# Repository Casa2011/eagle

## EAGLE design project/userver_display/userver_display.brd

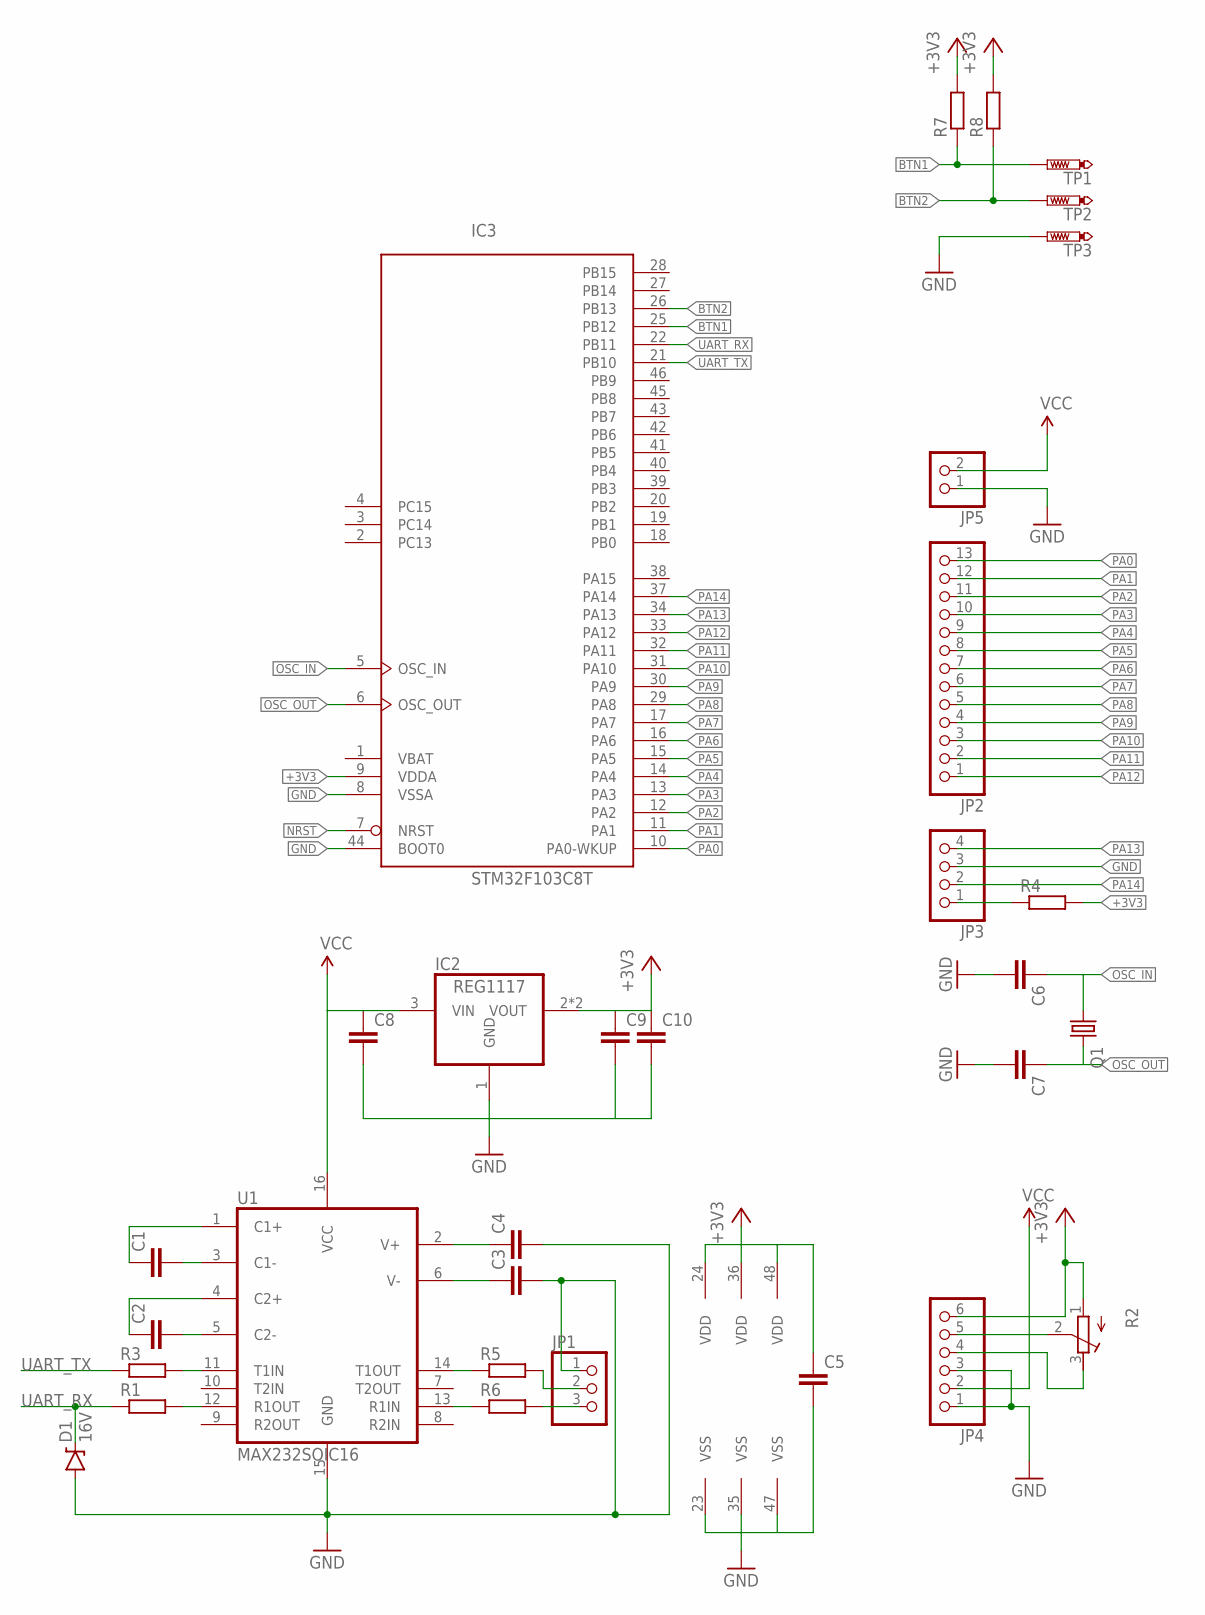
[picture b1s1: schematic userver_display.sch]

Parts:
C1, C2, C3, C4, C5, C8, C9, C10: CC0805; C0805
C6, C7: CC0603; C0603
D1: 16V; SOD-123
IC2: REG1117; SOT223
IC3: STM32F103C8T; LQFP48
JP1: PINHD-1X3; 1X03
JP2: PINHD-1X13; 1X13
JP3: PINHD-1X4; 1X04
JP4: PINHD-1X6; 1X06
JP5: PINHD-1X2; 1X02
Q1: CRYSTALHC49UP; HC49UP
R1, R3, R4, R5, R6, R7, R8: R0603; 0603
R2: R-TRIMM64P; RTRIM64P
TP1, TP2, TP3: PTR1TP10SQ; TP10SQ
U1: MAX232SOIC16; SO016

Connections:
+3V3: C5.1, C9.1, C10.1, IC2.2 (VOUT), IC2.4 (VOUT), IC3.9 (VDDA), IC3.24 (VDD), IC3.36 (VDD), IC3.48 (VDD), JP4.6, R2.1 (A), R4.2, R7.2, R8.2
BTN1: IC3.25 (PB12), R7.1, TP1.TP
BTN2: IC3.26 (PB13), R8.1, TP2.TP
GND: C3.2, C4.2, C5.2, C6.2, C7.2, C8.2, C9.2, C10.2, D1.A, IC2.1 (GND), IC3.8 (VSSA), IC3.23 (VSS), IC3.35 (VSS), IC3.44 (BOOT0), IC3.47 (VSS), JP1.1, JP3.3, JP4.1, JP4.3, JP5.1, TP3.TP, U1.15 (GND)
unnamed: JP1.2, R5.2
unnamed: JP1.3, R6.2
unnamed: C2.1, U1.4 (C2+)
unnamed: C2.2, U1.5 (C2-)
unnamed: C1.2, U1.3 (C1-)
unnamed: C1.1, U1.1 (C1+)
unnamed: C3.1, U1.6 (V-)
unnamed: R1.2, U1.12 (R1OUT)
unnamed: R3.2, U1.11 (T1IN)
unnamed: C4.1, U1.2 (V+)
unnamed: R6.1, U1.13 (R1IN)
unnamed: R5.1, U1.14 (T1OUT)
unnamed: JP4.4, R2.3 (E)
unnamed: JP4.5, R2.2 (S)
NRST: IC3.7 (NRST), JP3.1, R4.1
OSC_IN: C6.1, IC3.5 (OSC_IN), Q1.1
OSC_OUT: C7.1, IC3.6 (OSC_OUT), Q1.2
PA0: IC3.10 (PA0-WKUP), JP2.13
PA1: IC3.11 (PA1), JP2.12
PA2: IC3.12 (PA2), JP2.11
PA3: IC3.13 (PA3), JP2.10
PA4: IC3.14 (PA4), JP2.9
PA5: IC3.15 (PA5), JP2.8
PA6: IC3.16 (PA6), JP2.7
PA7: IC3.17 (PA7), JP2.6
PA8: IC3.29 (PA8), JP2.5
PA9: IC3.30 (PA9), JP2.4
PA10: IC3.31 (PA10), JP2.3
PA11: IC3.32 (PA11), JP2.2
PA12: IC3.33 (PA12), JP2.1
PA13: IC3.34 (PA13), JP3.4
PA14: IC3.37 (PA14), JP3.2
UART_RX: D1.C, IC3.22 (PB11), R1.1
UART_TX: IC3.21 (PB10), R3.1
VBAT: IC3.1 (VBAT)
VCC: C8.1, IC2.3 (VIN), JP4.2, JP5.2, U1.16 (VCC)

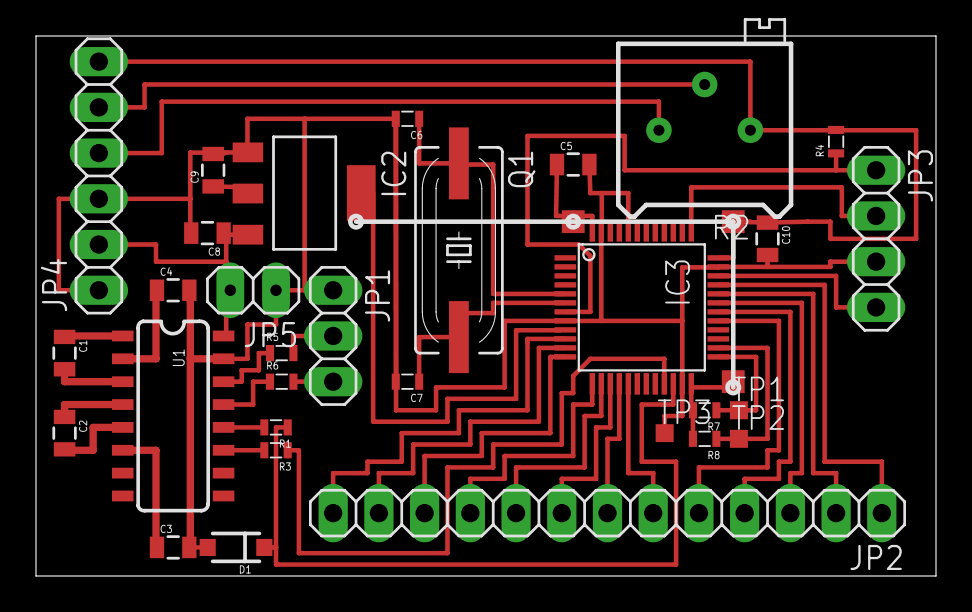
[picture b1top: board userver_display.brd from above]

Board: 2 copper layers, 50.0 x 30.0 mm, 31 parts (0 on the bottom side), 39 nets.

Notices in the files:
parts and their libraries:
SparkFun-DigitalIC: Licensing: Creative Commons ShareAlike 4.0 International - https://creativecommons.org/licenses/by-sa/4.0
